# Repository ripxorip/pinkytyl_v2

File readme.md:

* Add all the libraries to the repo [Done]
* Bug for next revision: HWB (Pin PE2 must be grounded for reset to work) - For now I can probably do a hack to force reset by holding key during startup somehow in QMK? [Done]
* Bug for next: uvcc to vbus for split detection? [Done]

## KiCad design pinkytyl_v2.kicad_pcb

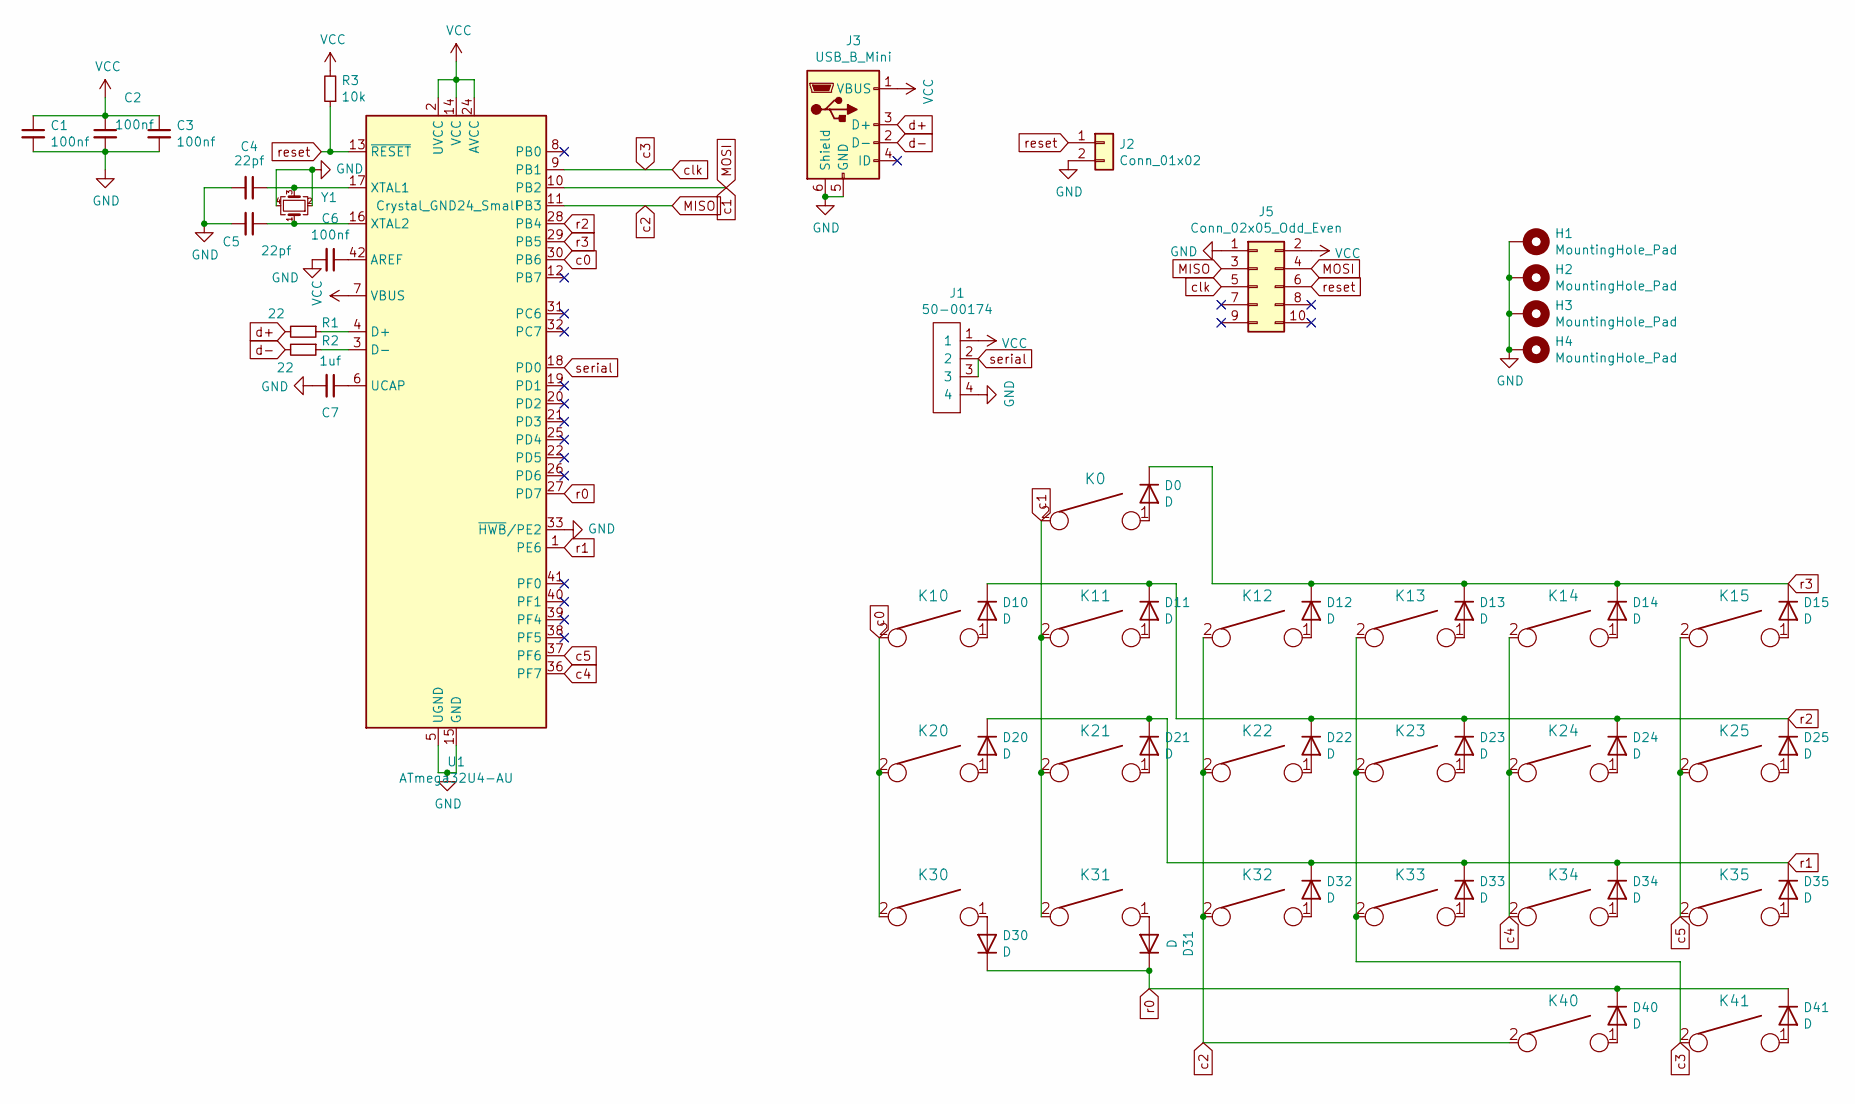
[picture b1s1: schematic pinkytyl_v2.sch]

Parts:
C1, C2, C3, C6: 100nf; C_0402_1005Metric; LCSC C1525
C4, C5: 22pf; C_0402_1005Metric; LCSC C1555
C7: 1uf; C_0402_1005Metric; LCSC C52923
D0, D10, D11, D12, D13, D14, D15, D20, D21, D22, D23, D24, D25, D30, D31, D32, D33, D34, D35, D40, D41: D; D_SOD-123; LCSC C81598
H1, H2, H3, H4: MountingHole_Pad; MountingHole_2.2mm_M2_Pad
J1: 50-00174; 54-00174
J2: Conn_01x02; PinHeader_1x02_P1.27mm_Vertical
J3: USB_B_Mini; USB_Micro-B_Molex-105017-0001
J5: Conn_02x05_Odd_Even; Tag-Connect_TC2050-IDC-NL_2x05_P1.27mm_Vertical
K0, K10, K11, K12, K13, K14, K15, K20, K21, K22, K23, K24, K25, K30, K31, K32, K33, K34, K35, K40, K41: KEYSW; SW_PG1350_reversible
R1, R2: 22; R_0402_1005Metric; LCSC C25092
R3: 10k; R_0402_1005Metric; LCSC C25744
U1: ATmega32U4-AU; TQFP-44_10x10mm_P0.8mm
Y1: Crystal_GND24_Small; Crystal_SMD_3225-4Pin_3.2x2.5mm; LCSC C13738

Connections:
GND: C1.2, C2.2, C3.2, C4.2, C5.2, C6.2, C7.2, H1.1, H2.1, H3.1, H4.1, J1.4, J2.2, J3.5 (GND), J3.6 (Shield), J5.1, U1.5 (UGND), U1.15 (GND), U1.23 (GND), U1.33 (~HWB~/PE2), U1.35 (GND), U1.43 (GND), Y1.2, Y1.4
MISO: J5.3, K12.2, K22.2, K32.2, K40.2, U1.11 (PB3)
MOSI: J5.4, K0.2, K11.2, K21.2, K31.2, U1.10 (PB2)
unnamed: C4.1, U1.17 (XTAL1), Y1.3
unnamed: C5.1, U1.16 (XTAL2), Y1.1
unnamed: C6.1, U1.42 (AREF)
unnamed: C7.1, U1.6 (UCAP)
unnamed: D0.2 (A), K0.1
unnamed: D10.2 (A), K10.1
unnamed: D11.2 (A), K11.1
unnamed: D12.2 (A), K12.1
unnamed: D13.2 (A), K13.1
unnamed: D14.2 (A), K14.1
unnamed: D15.2 (A), K15.1
unnamed: D20.2 (A), K20.1
unnamed: D21.2 (A), K21.1
unnamed: D22.2 (A), K22.1
unnamed: D23.2 (A), K23.1
unnamed: D24.2 (A), K24.1
unnamed: D25.2 (A), K25.1
unnamed: D30.2 (A), K30.1
unnamed: D31.2 (A), K31.1
unnamed: D32.2 (A), K32.1
unnamed: D33.2 (A), K33.1
unnamed: D34.2 (A), K34.1
unnamed: D35.2 (A), K35.1
unnamed: D40.2 (A), K40.1
unnamed: D41.2 (A), K41.1
unnamed: R1.1, U1.4 (D+)
unnamed: R2.1, U1.3 (D-)
VCC: C1.1, C2.1, C3.1, J1.1, J3.1 (VBUS), J5.2, R3.2, U1.2 (UVCC), U1.7 (VBUS), U1.14 (VCC), U1.24 (AVCC), U1.34 (VCC), U1.44 (AVCC)
c0: K10.2, K20.2, K30.2, U1.30 (PB6)
c3: J5.5, K13.2, K23.2, K33.2, K41.2, U1.9 (PB1)
c4: K14.2, K24.2, K34.2, U1.36 (PF7)
c5: K15.2, K25.2, K35.2, U1.37 (PF6)
d+: J3.3 (D+), R1.2
d-: J3.2 (D-), R2.2
r0: D30.1 (K), D31.1 (K), D40.1 (K), D41.1 (K), U1.27 (PD7)
r1: D20.1 (K), D21.1 (K), D32.1 (K), D33.1 (K), D34.1 (K), D35.1 (K), U1.1 (PE6)
r2: D10.1 (K), D11.1 (K), D22.1 (K), D23.1 (K), D24.1 (K), D25.1 (K), U1.28 (PB4)
r3: D0.1 (K), D12.1 (K), D13.1 (K), D14.1 (K), D15.1 (K), U1.29 (PB5)
reset: J2.1, J5.6, R3.1, U1.13 (~RESET)
serial: J1.2, J1.3, U1.18 (PD0)

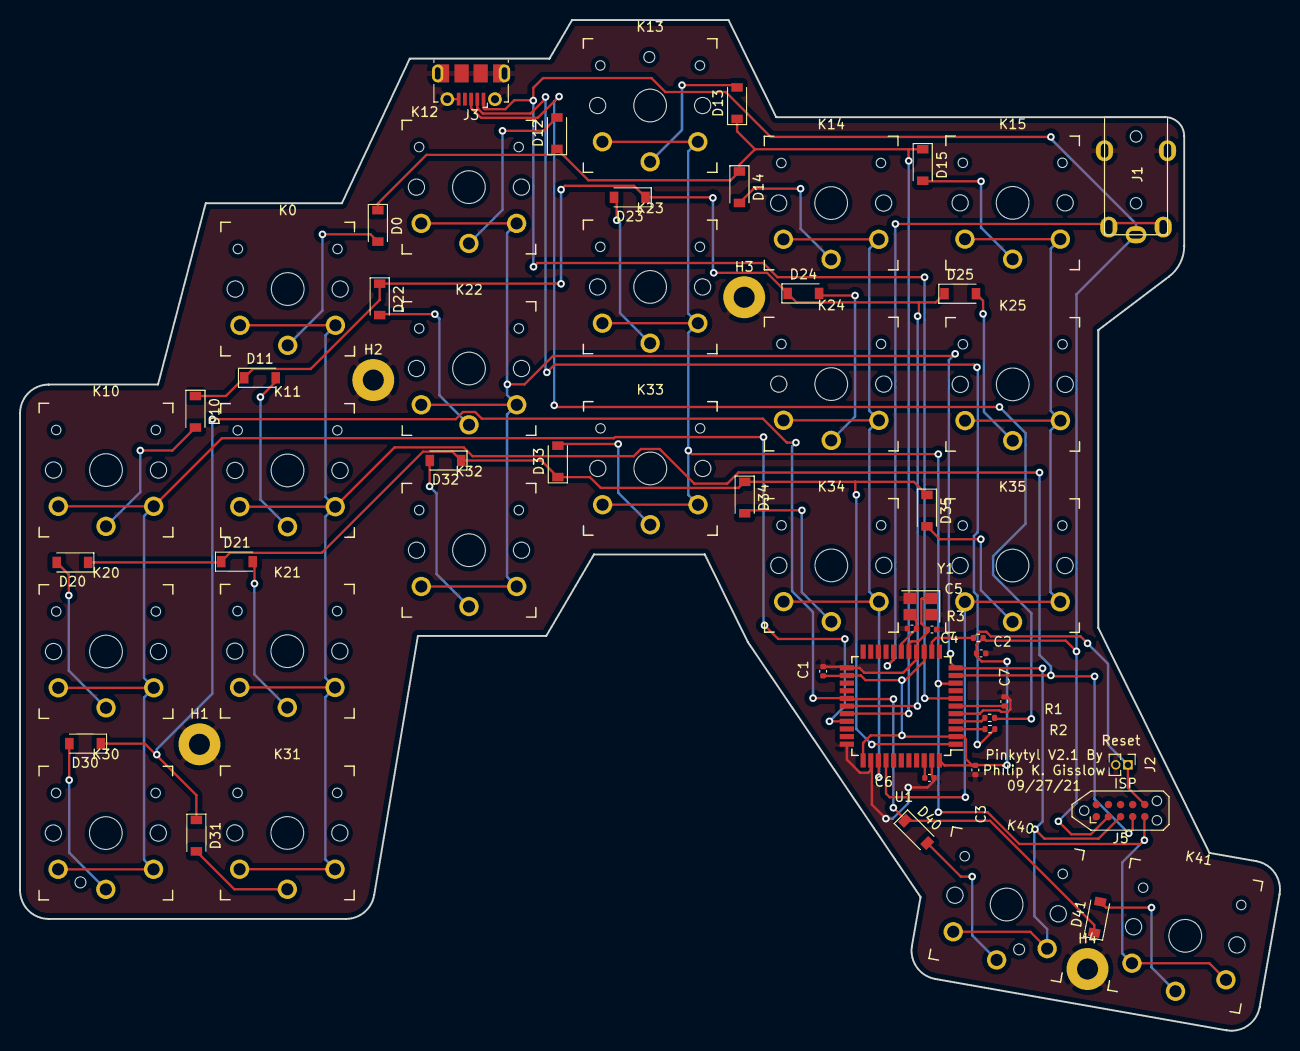
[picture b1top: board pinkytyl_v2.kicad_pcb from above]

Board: 2 copper layers, 132.0 x 105.9 mm, 62 parts (0 on the bottom side), 43 nets.

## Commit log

2021-09-19 Initial commit for pinkytyl V2
2021-09-21 Adds MU version and initial placing
2021-09-22 First potentially working version
2021-09-23 DRC passing and is now double sided
2021-09-23 Adds smaller version of the 3.5mm connector
2021-09-23 Cound be final
2021-09-23 In the middle of slim redesign
2021-09-24 Keys wired
2021-09-24 Routing complete, time for review
2021-09-24 Adds mounting holes
2021-09-24 Adds JLCPCB part numbers
2021-09-27 Rough layout, might be ready for order
2021-09-27 Adds name to silkscreen
2021-10-18 Adds external dependencies in lib/
2021-10-18 Initial commit for chocs
2021-10-18 Changed my mind regarding detection of VUSB, software solution is doing fine with less components
